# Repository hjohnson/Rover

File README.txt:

Introduction:
      This time, I'm presenting a whole robot, a project that has a slightly larger scale than my normal ones. This robot (or rover) was designed as an educational tool, a project to be built by teams of High School students over a period of 2-3 weeks. ÊAs such, the robot was designed for simplicity and durability, not low price. The robotÕs design is split into several modules: Mechanical Frame, Locomotion, Sensors, and Control. 

Mechanical Frame: 
	Material: The frame is constructed from four 1Ó width 80/20 extruded aluminum rails. For those who donÕt know, the 80/20 T-slot system is called Òthe industrial erector set,Ó and the description is fitting. The rails can be cut to size relatively easily with hand tools (though we use power tools,) and can be bolted together using aluminum plates, ÒT-nutsÓ and screws, instead of welding. This means that the system is easily reconfigurable on the fly, and small mistakes can be quickly remedied by loosening the plates and shifting the rail, instead of by removing welds.  
	Design: The main frame is a simple rectangle constructed from four lengths of 80/20 rail, bolted together at the corners with four triangular plates.  Attached to this main frame are several other lengths of rail. One houses the bumper; another houses the ball transport and vulnerability switch. (All of which will be discussed later) Three vertical stalks are also integrated into the design to hold other sensors. As a side bonus, these stalks are mounted firmly enough that the robot can technically be flipped upside down and rest on them, for easier service.

Locomotion:
	Mechanical Drive System: The robot incorporates two pneumatic wheels with integrated sprockets. The two wheels can rotate independently of each other, enabling steering, and are attached to a single axle, which is a 1/2-inch outside diameter tube. This axle is attached to the underside of the frame using pillow blocks.  Two 8-amp stepper motors drive the 2 wheels through a chain system. Sprockets attach to the motorsÕ drive shafts, and connect to the wheel-mounted sprockets through lengths of chain.  
	Motor Control System: A pair of Anaheim Automation MBC10101 Stepper Motor Drivers control the stepper motors. These drivers are powered by 24V provided by the robotÕs power unit, and have control inputs driven by the main control card. The main controls are: clock input, to determine the speed of the motors; Inhibit, to remove power from the motors and stop the robot; and Direction, to control the direction of rotation. These inputs are controlled by the main board, which will be discussed later. These drivers, while expensive, are from my experience highly reliable and are hard to burn, an excellent feature when wired by inexperienced builders who can easily miss a ground or clock signal. 
	Electrical Supply (power unit): The robotÕs power is provided by a custom supply based around two 12V, 2200mAh, Lead-Acid rechargeable batteries. When in Charge mode, the power supply wires these two batteries in parallel, each with their own 10 ohm ceramic power resistor, to the main power jack. While in this mode, ~14V can be supplied from an external regulated supply to charge the batteries. When in Drive mode, the power supply switches the two batteries into series, providing 24V output to the main power jack, which runs to the stepper motor drivers. The power supply also taps one of the batteries to supply 12V to a 7805 5V voltage regulator, which powers the control circuitry. Due to the power dissipation through this 7805, it is screwed to a Òheat sinkÓ (bottle cap). 

Sensors:
	The robot integrates several sensors to react to its surroundings. These include front-mounted bumper switches and phototransistors, and a rear-mounted vulnerability switch. 
	Bumper: A flexible bumper is attached to the front of the robot, along with 2 momentary lever switches. This enables the robot to detect when it has run into an object, usually the wall. The robotÕs response to this information can be determined in software by the students.
	Vulnerability Switch: A 3 position (SPTT) toggle switch is mounted to the rear of the robot, and acts as a manual shutdown switch and Òweak spot.Ó When the switch is positioned in the center (not connected), the robot operates normally. However, when the switch is actuated to either side, the robot instantly shuts down, turning off the motors and rendering the robot inoperable. This feature is implemented in software, but tampering with that section of code is forbidden. This switch is primarily used as a safety feature, but is also exploited for the high school competition, as bonus points are awarded to teams who can activate their opponentsÕ switches. 
	Phototransistors: While these are not currently attached, the phototransistors can be used to detect light levels, allowing the robots to navigate based on guidance from a flashlight, as well as to seek out the beacons above the competitionÕs Ògoals.Ó 

Control:
	At last, the more recognizable part. The robotÕs control system is remarkably simple, consisting of an Arduino-based card and an associated remote control.
	Control Card Hardware: 
      The actual circuitry on the card is remarkably simple, and primarily consists of an Arduino microprocessor, an XBee wireless transceiver, and some support circuitry.
       Motor Control: The Arduino output pins are buffered through 74LS14 hex inverters and then sent to the stepper motor drivers and the inputs from the bumper and vulnerability switches. The outputs are pulled up through resistors to 5V to ensure that the drivers are properly driven, as we had previously encountered problems where the ArduinoÕs output pins couldnÕt sufficiently drive the motor driversÕ input pins. 
      Sensors: The sensor inputs are buffered as well to form an extremely simple debouncing circuit. The Phototransistors also run through 1.5K resistors to ground, forming common collector amplifiers whose outputs run into the Analog In pins on the Arduino. 
      XBee: The control card utilizes an XBee wireless transceiver to enable bidirectional serial communication between the robot and the remote control. An Adafruit XBee Adapter kit is used to house the XBee and convert the ArduinoÕs 5V logic to the XBeeÕs 3.3V logic.  
	Control Card Software: 
      Motor Control: The top of the CardÕs priority list is controlling the motor drivers. Each of these drivers takes 3 inputs (clock, inhibit, and direction) as discussed previously. The 2 clock lines are driven by independent square waves generated by the Arduino Tone library. These square waves typically have frequencies between 2KHz and 5KHz.  Because the stepper motors have 200 steps/rotation, these speeds translate to motor speeds between 10 and 25 motor revolutions per second. However, due to the gearing present through the sprockets, the robotÕs wheels rotate at a lesser rate. (Embarrassingly, I havenÕt actually counted sprocket teeth or done the rest of this math yet. IÕll get back to you.) Inhibit and Direction, the other 2 data lines (per driver) are comparatively simple. When the driver sees a logic low on the inhibit pin, the motor is turned on, and when the driver sees a logic high, the motors are turned off. Similarly, for direction, logic low results in forward rotation, logic high results in backwards rotation. 
      Vulnerability Switch: The vulnerability switch input is monitored using an interrupt, whose interrupt service routine disables both motors, then waits for the vulnerability switch to be returned to center before exiting. In this way, the motors are disabled upon the switch being flicked, and will not re-enable, no matter what the user says, until the switch is returned to center.
      XBee Remote Control: To communicate through the XBee, a simple serial protocol is used, along with a pre-determined command set. Incoming serial bytes are read and interpreted by the program, with, for example, ÒWÓ signifying forward movement, ÒSÓ signifying backward movement, and ÒFÓ signifying stop. For more information about this process, look at the previous article, about the Remote Control designed to interface with this system.

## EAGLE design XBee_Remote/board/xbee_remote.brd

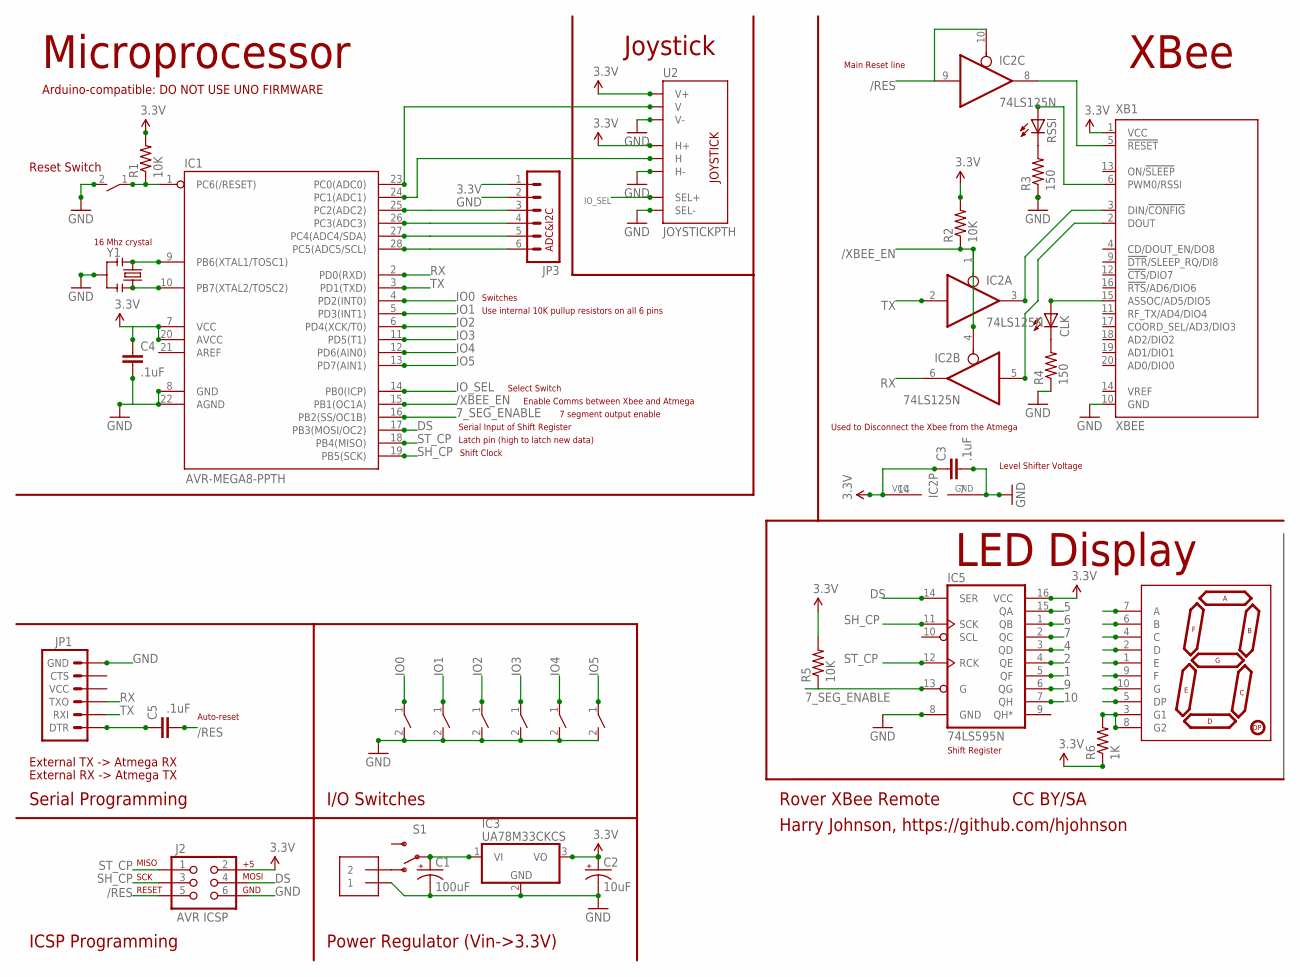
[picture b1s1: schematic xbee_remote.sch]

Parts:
C1: 100uF; CPOL-RADIAL-100UF-25V
C2: 10uF; CPOL-RADIAL-10UF-25V
C3, C4, C5: .1uF; CAP-PTH-SMALL2
CLK: LED3MM
IC1: AVR-MEGA8-PPTH; DIL28-3
IC2: 74LS125N; DIL14
IC3: UA78M33CKCS; TO220V
IC5: 74LS595N; DIL16
J1: 1X2-3.5MM; 3.5MMTERM
J2: AVR ICSP; 2X3
JP1: ARDUINO_SERIAL_PROGRAMPTH; 1X06
JP3: M06SIP; 1X06
R1, R2, R5: 10K; 0207/10
R3, R4: 150; 0207/10
R6: 1K; 0207/10
RSSI: LED3MM
S1: SWITCH-SPSTPTH; SWITCH-SPDT
U2: JOYSTICKPTH; JOYSTICK
U$4: 7-SEGMENT-DISPLAY-1"-RED; 7-SEGMENT-1"PTH
U$8, U$9, U$10, U$11, U$12, U$13, U$14: TACT_TL1107
XB1: XBEE
Y1: RESONATORPTH; RESONATOR-PTH

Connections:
1: IC5.5 (QF), U$4.1 (E)
2: IC5.4 (QE), U$4.2 (D)
3.3V: C2.1 (+), C3.1, C4.1, IC1.7 (VCC), IC1.20 (AVCC), IC2.14 (VCC), IC3.3 (VO), IC5.16 (VCC), J2.2, JP3.1, R1.2, R2.2, R5.2, R6.1, U2.H1 (H+), U2.V1 (V+), XB1.1 (VCC)
3V3_/RST: IC2.8 (O), XB1.5 (!RESET)
3V3_RX: IC2.5 (I), XB1.2 (DOUT)
3V3_TX: IC2.3 (O), XB1.3 (DIN/!CONFIG)
4: IC5.3 (QD), U$4.4 (C)
5: IC5.15 (QA), U$4.5 (DP)
6: IC5.1 (QB), U$4.6 (B)
7: IC5.2 (QC), U$4.7 (A)
7_SEG_ENABLE: IC1.16 (PB2(SS/OC1B)), IC5.13 (G), R5.1
9: IC5.6 (QG), U$4.9 (F)
10: IC5.7 (QH), U$4.10 (G)
/RES: C5.2, IC1.1 (PC6(/RESET)), IC2.9 (I), IC2.10 (OE), J2.5, R1.1, U$8.1
/XBEE_EN: IC1.15 (PB1(OC1A)), IC2.1 (OE), IC2.4 (OE), R2.1
A2: IC1.25 (PC2(ADC2)), JP3.3
A3: IC1.26 (PC3(ADC3)), JP3.4
DS: IC1.17 (PB3(MOSI/OC2)), IC5.14 (SER), J2.4
GND: C1.2 (-), C2.2 (-), C3.2, C4.2, IC1.8 (GND), IC1.22 (AGND), IC2.7 (GND), IC3.2 (GND), IC5.8 (GND), J1.1, J2.6, JP1.6 (GND), JP3.2, R3.1, R4.1, U2.B2A (SEL-), U2.H3 (H-), U2.V3 (V-), U$8.2, U$9.2, U$10.2, U$11.2, U$12.2, U$13.2, U$14.2, XB1.10 (GND), Y1.2
IO0: IC1.4 (PD2(INT0)), U$9.1
IO1: IC1.5 (PD3(INT1)), U$10.1
IO2: IC1.6 (PD4(XCK/T0)), U$11.1
IO3: IC1.11 (PD5(T1)), U$12.1
IO4: IC1.12 (PD6(AIN0)), U$13.1
IO5: IC1.13 (PD7(AIN1)), U$14.1
IO_SEL: IC1.14 (PB0(ICP)), U2.B1A (SEL+)
unnamed: IC1.9 (PB6(XTAL1/TOSC1)), Y1.1
unnamed: IC1.10 (PB7(XTAL2/TOSC2)), Y1.3
unnamed: J1.2, S1.1 (O)
unnamed: C5.1, JP1.1 (DTR)
unnamed: R6.2, U$4.3 (G1), U$4.8 (G2)
unnamed: RSSI.A, XB1.6 (PWM0/RSSI)
unnamed: R3.2, RSSI.K (C)
unnamed: CLK.A, XB1.15 (ASSOC/AD5/DIO5)
unnamed: CLK.K (C), R4.2
RX: IC1.2 (PD0(RXD)), IC2.6 (O), JP1.3 (TXO)
SCL: IC1.28 (PC5(ADC5/SCL)), JP3.6
SDA: IC1.27 (PC4(ADC4/SDA)), JP3.5
SH_CP: IC1.19 (PB5(SCK)), IC5.11 (SCK), J2.3
ST_CP: IC1.18 (PB4(MISO)), IC5.12 (RCK), J2.1
TX: IC1.3 (PD1(TXD)), IC2.2 (I), JP1.2 (RXI)
VIN: C1.1 (+), IC3.1 (VI), S1.2
VIN_H: IC1.24 (PC1(ADC1)), U2.H2 (H)
VIN_V: IC1.23 (PC0(ADC0)), U2.V2 (V)

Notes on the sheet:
LED Display
Serial Programming
Microprocessor
Rover XBee Remote
Harry Johnson, https://github.com/hjohnson
CC BY/SA
ICSP Programming
Power Regulator (Vin->3.3V)
XBee
Shift Clock
Latch pin (high to latch new data)
Serial Input of Shift Register
7 segment output enable
Enable Comms between Xbee and Atmega
Select Switch
ADC&I2C
External TX -> Atmega RX
External RX -> Atmega TX
I/O Switches
Joystick
Switches
Use internal 10K pullup resistors on all 6 pins
16 Mhz crystal
Main Reset line
Used to Disconnect the Xbee from the Atmega
Auto-reset
Reset Switch
Arduino-compatible: DO NOT USE UNO FIRMWARE
Level Shifter Voltage
Shift Register

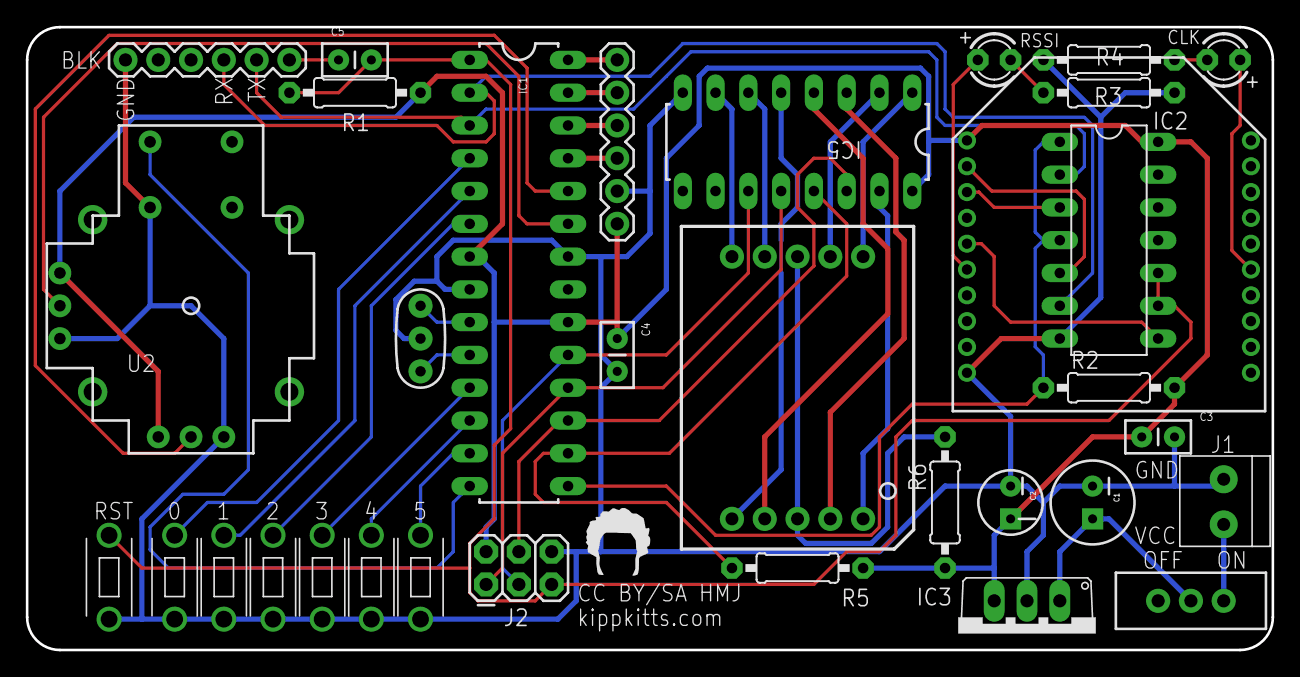
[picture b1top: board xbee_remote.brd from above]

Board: 2 copper layers, 96.5 x 48.3 mm, 34 parts (0 on the bottom side), 44 nets.

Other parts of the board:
U$2: TOP_DOCU_5MM

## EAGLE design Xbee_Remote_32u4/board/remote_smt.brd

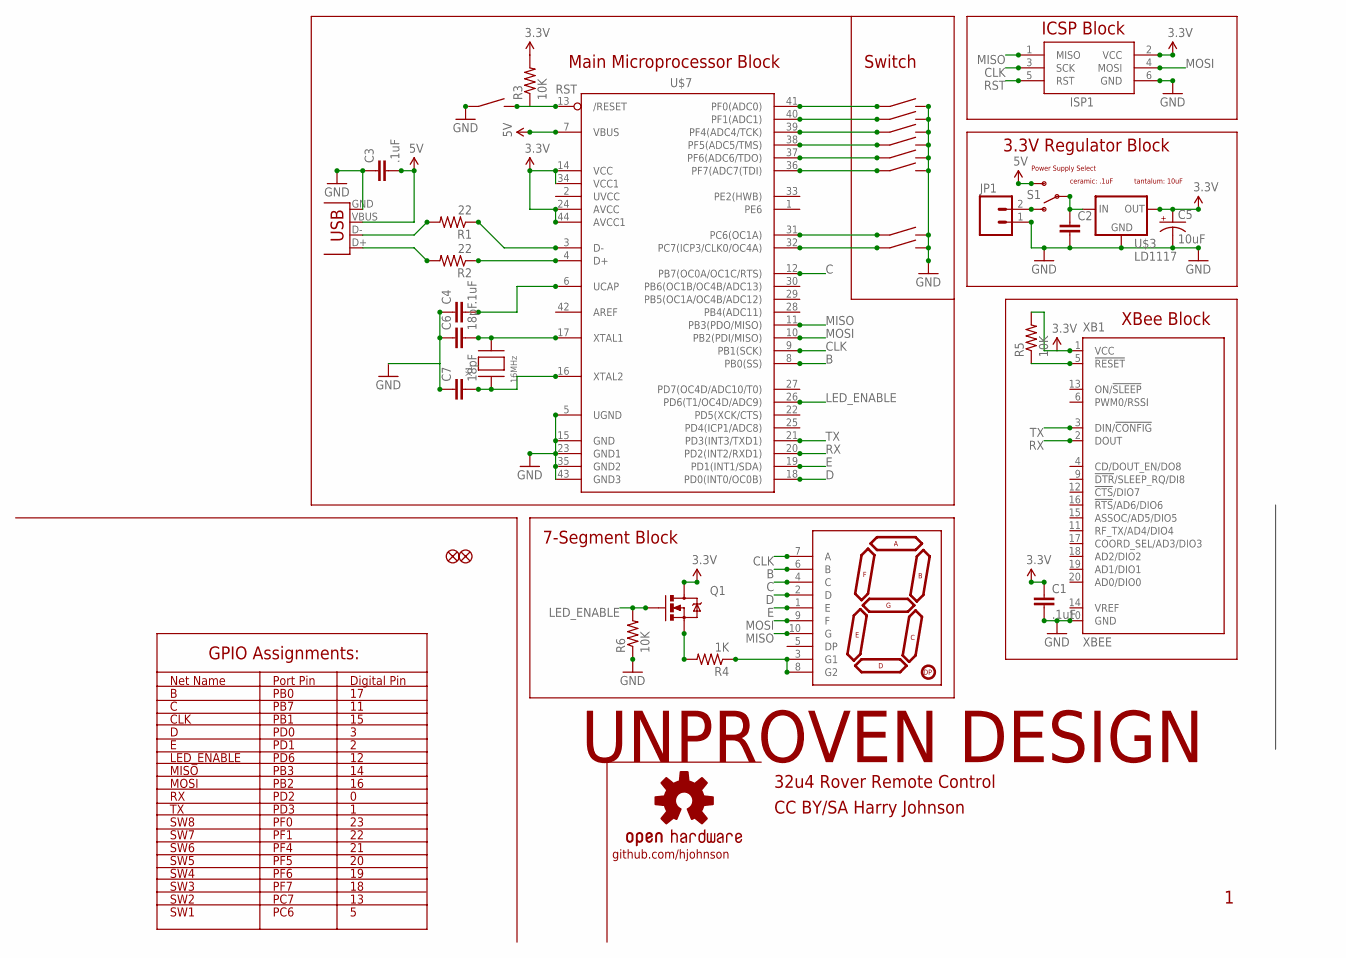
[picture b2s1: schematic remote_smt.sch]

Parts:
C1, C3, C4: .1uF; 0805
C2: CAP0805; 0805
C5: 10uF; EIA3528-KIT
C6, C7: 18pF; 0805
ISP1: AVRISP-6; AVRISP
JP1: M023.5MM; SCREWTERMINAL-3.5MM-2
JP2, JP3: FIDUCIAL1.5X3; FIDUCIAL-1.5X3
Q1: MOSFET-NCHANNELSMD; SOT23-3
R1, R2: 22; 0805
R3, R5, R6: 10K; 0805
R4: 1K; 0805
S1: SWITCH-SPSTKIT; SWITCH-SPDT_KIT
U$1: 7-SEGMENT-DISPLAY-1"-RED; 7-SEGMENT-1"PTH
U$2, U$6, U$8, U$11, U$12, U$13, U$14, U$15, U$17: SPST_SWITCH; EG2513-ND
U$3: LD1117; SOT223
U$7: ATMEGA32U4-AU; TQFP44
U$10: OSHW-LOGOL; OSHW-LOGO-L
X1: 16MHz; NX5032
X2: USBPTH; USB-B-PTH
XB1: XBEE

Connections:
3.3V: C1.1, C5.A (+), ISP1.2 (VCC), Q1.3 (D), R3.2, R5.2, U$3.2 (OUT), U$7.14 (VCC), U$7.24 (AVCC), U$7.34 (VCC1), U$7.44 (AVCC1), XB1.1 (VCC)
5V: C3.2, S1.3 (S), U$7.7 (VBUS), X2.VBUS
B: U$1.6 (B), U$7.8 (PB0(SS))
C: U$1.4 (C), U$7.12 (PB7(OC0A/OC1C/RTS))
CLK: ISP1.3 (SCK), U$1.7 (A), U$7.9 (PB1(SCK))
D: U$1.2 (D), U$7.18 (PD0(INT0/OC0B))
E: U$1.1 (E), U$7.19 (PD1(INT1/SDA))
GND: C1.2, C2.2, C3.1, C4.1, C5.C (-), C6.1, C7.1, ISP1.6 (GND), JP1.1, R6.1, U$2.P$1 (1), U$3.1 (GND), U$3.4 (GND), U$6.P$2 (2), U$7.5 (UGND), U$7.15 (GND), U$7.23 (GND1), U$7.35 (GND2), U$7.43 (GND3), U$8.P$2 (2), U$11.P$2 (2), U$12.P$2 (2), U$13.P$2 (2), U$14.P$2 (2), U$15.P$2 (2), U$17.P$2 (2), X2.GND, XB1.10 (GND)
LED_ENABLE: Q1.1 (G), R6.2, U$7.26 (PD6(T1/OC4D/ADC9))
MISO: ISP1.1 (MISO), U$1.10 (G), U$7.11 (PB3(PDO/MISO))
MOSI: ISP1.4 (MOSI), U$1.9 (F), U$7.10 (PB2(PDI/MISO))
unnamed: C6.2, U$7.17 (XTAL1), X1.P$2
unnamed: C7.2, U$7.16 (XTAL2), X1.P$1
unnamed: R1.1, U$7.3 (D-)
unnamed: R2.1, U$7.4 (D+)
unnamed: R2.2, X2.D+
unnamed: R1.2, X2.D-
unnamed: R4.1, U$1.3 (G1), U$1.8 (G2)
unnamed: C4.2, U$7.6 (UCAP)
unnamed: Q1.2 (S), R4.2
unnamed: JP1.2, S1.1 (O)
unnamed: C2.1, S1.2, U$3.3 (IN)
RST: ISP1.5 (RST), R3.1, U$2.P$2 (2), U$7.13 (/RESET)
RX: U$7.20 (PD2(INT2/RXD1)), XB1.2 (DOUT)
SW1: U$6.P$1 (1), U$7.31 (PC6(OC1A))
SW2: U$7.32 (PC7(ICP3/CLK0/OC4A)), U$8.P$1 (1)
SW3: U$7.36 (PF7(ADC7(TDI)), U$17.P$1 (1)
SW4: U$7.37 (PF6(ADC6/TDO)), U$15.P$1 (1)
SW5: U$7.38 (PF5(ADC5/TMS)), U$14.P$1 (1)
SW6: U$7.39 (PF4(ADC4/TCK)), U$13.P$1 (1)
SW7: U$7.40 (PF1(ADC1)), U$12.P$1 (1)
SW8: U$7.41 (PF0(ADC0)), U$11.P$1 (1)
TX: U$7.21 (PD3(INT3/TXD1)), XB1.3 (DIN/!CONFIG)
XBEE_RST: R5.1, XB1.5 (!RESET)

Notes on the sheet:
Net Name
Digital Pin
CLK
LED_ENABLE
MISO
MOSI
Port Pin
PB0
PB7
PB1
PD0
PD1
PD6
PB3
PB2
PD2
PD3
SW8
SW7
SW6
SW5
SW4
SW3
SW2
SW1
PF0
PF1
PF4
PF5
PF6
PF7
PC7
PC6
GPIO Assignments:
3.3V Regulator Block
ICSP Block
XBee Block
7-Segment Block
Main Microprocessor Block
Switch

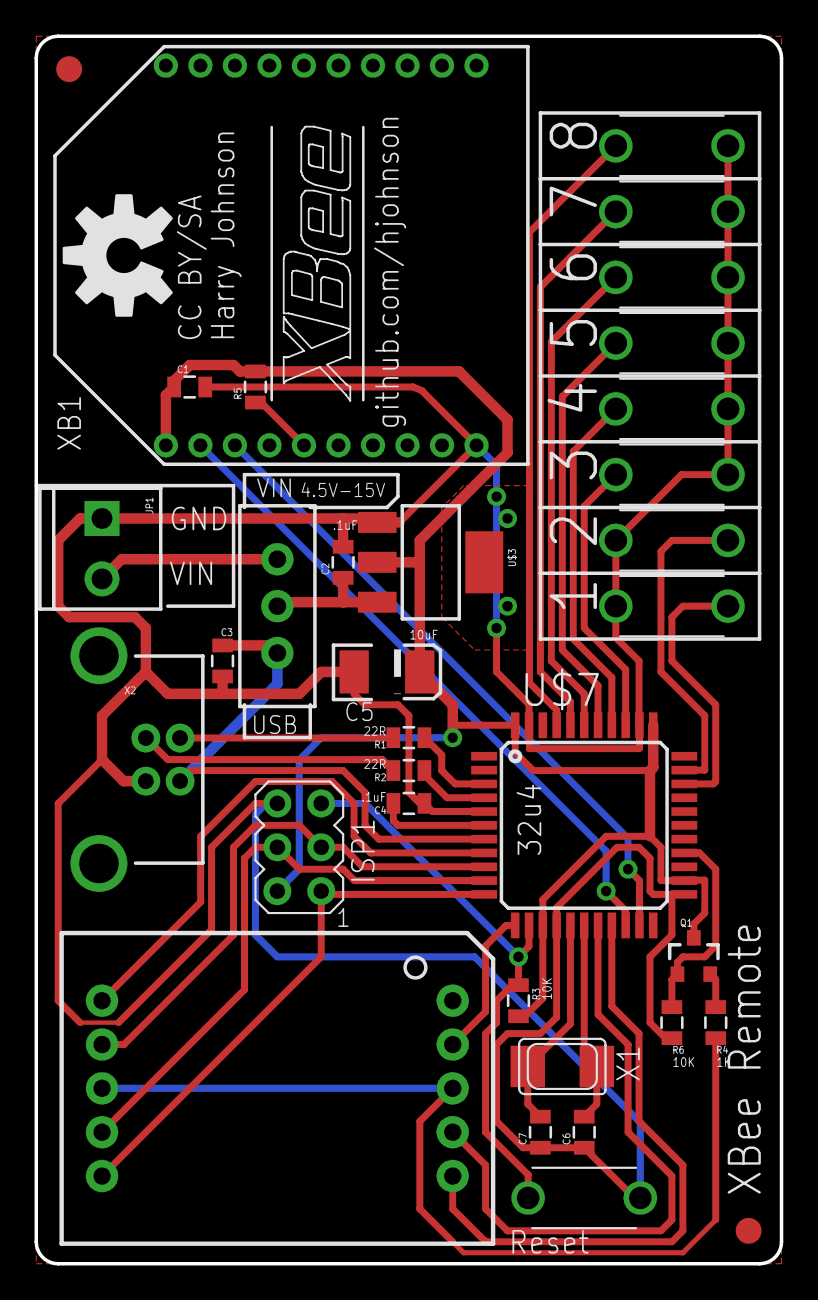
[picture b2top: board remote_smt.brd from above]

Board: 2 copper layers, 43.2 x 71.1 mm, 35 parts (0 on the bottom side), 34 nets.

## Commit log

2011-12-18 added various stuff
2012-01-12 Added various files, including gerbers
2012-01-12 Added copyGerber bash script.
2012-01-26 UNTESTED: 32u4 based remote control
    Schematic, board, and .ino files for a atmega32u4 based XBee remote
    control for the rover.
2012-01-31 Updated through-hole board and schematic
    Changed polygon fill to hatch, fully routed the board to not need
    polygon, just in case, cleaned up the schematic, and added a net list
    to the schematic.
2012-01-31 Fixed up SMT version, added some files zipped.
2012-02-02 Made a bunch of changes.
    Most importantly: Switched the lines for Switch 6 and XBee enable, to
    make routing more sensible, and to make reading of switches take a
    single for loop.
2012-02-19 Updated the schematic and board, and updated the writeup immensely.
2012-04-23 Added a writeup and a PDF of the schematic and board for easier viewing (w/o EAGLE)
2012-04-29 New revision of remote: Added joystick, shifted parts.
2012-05-04 Removed zip file, updated example code to include joystick

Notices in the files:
XBee_Remote/board/xbee_remote.brd:
CC BY/SA HMJ
Xbee_Remote_32u4/board/remote_smt.sch:
CC BY/SA Harry Johnson
parts and their libraries:
SparkFun: Licensing: CC v3.0 Share-Alike You are welcome to use this library for commercial purposes.
